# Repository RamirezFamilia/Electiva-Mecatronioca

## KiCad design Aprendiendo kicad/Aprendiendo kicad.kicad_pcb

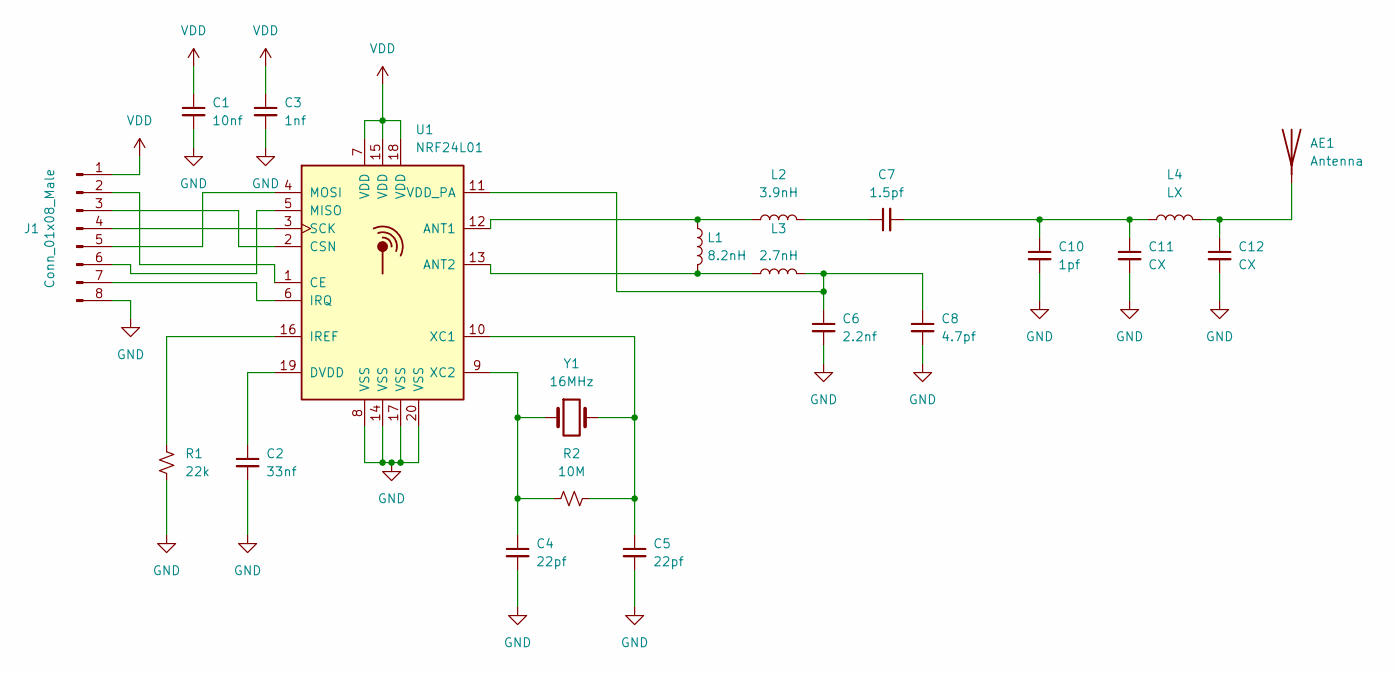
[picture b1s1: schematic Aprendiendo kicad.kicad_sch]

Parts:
AE1: Antenna; Texas_SWRA117D_2.4GHz_Right
C1: 10nf; C_0402_1005Metric
C2: 33nf; C_0402_1005Metric
C3: 1nf; C_0402_1005Metric
C4, C5: 22pf; C_0402_1005Metric
C6: 2.2nf; C_0402_1005Metric
C7: 1.5pf; C_0402_1005Metric
C8: 4.7pf; C_0402_1005Metric
C10: 1pf; C_0402_1005Metric
C11, C12: CX; C_0402_1005Metric
J1: Conn_01x08_Male; Hirose_DF13-08P-1.25DSA_1x08_P1.25mm_Vertical
L1: 8.2nH; L_0402_1005Metric
L2: 3.9nH; L_0402_1005Metric
L3: 2.7nH; L_0402_1005Metric
L4: LX; L_0402_1005Metric
R1: 22k; R_0402_1005Metric
R2: 10M; R_0402_1005Metric
U1: NRF24L01; QFN-20-1EP_4x4mm_P0.5mm_EP2.5x2.5mm
Y1: 16MHz; Crystal_SMD_3215-2Pin_3.2x1.5mm

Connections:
GND: C1.2, C2.2, C3.2, C4.2, C5.2, C6.2, C8.2, C10.2, C11.2, C12.2, J1.8, R1.2, U1.8 (VSS), U1.14 (VSS), U1.17 (VSS), U1.20 (VSS)
unnamed: AE1.1 (A), C12.1, L4.2
unnamed: C2.1, U1.19 (DVDD)
unnamed: C4.1, R2.1, U1.9 (XC2), Y1.1
unnamed: C5.1, R2.2, U1.10 (XC1), Y1.2
unnamed: C6.1, C8.1, L3.2, U1.11 (VDD_PA)
unnamed: C7.1, L2.2
unnamed: C7.2, C10.1, C11.1, L4.1
unnamed: J1.2, U1.1 (CE)
unnamed: J1.3, U1.2 (CSN)
unnamed: J1.4, U1.3 (SCK)
unnamed: J1.5, U1.4 (MOSI)
unnamed: J1.6, U1.5 (MISO)
unnamed: J1.7, U1.6 (IRQ)
unnamed: L1.1, L2.1, U1.12 (ANT1)
unnamed: L1.2, L3.1, U1.13 (ANT2)
unnamed: R1.1, U1.16 (IREF)
VDD: C1.1, C3.1, J1.1, U1.7 (VDD), U1.15 (VDD), U1.18 (VDD)

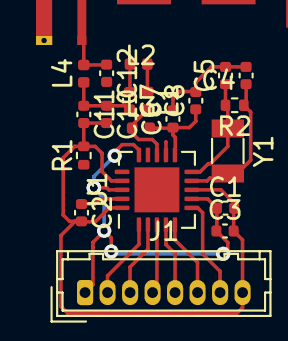
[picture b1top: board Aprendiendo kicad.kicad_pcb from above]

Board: 2 copper layers, 21 parts (0 on the bottom side), 18 nets.
